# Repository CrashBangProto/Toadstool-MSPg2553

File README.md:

#Toadstool-MSPg2553

**Toadstool Development Board - MSP430G2553**

The Toadstool family is made up of breadboard-friendly prototyping boards that house a microcontroller, and modules called *Caps* that connect using a standard header.  The prototyping board is analagous to an Arduino/Launchpad and the Cap analagous to a shield/boosterpack.

This repository contains the schematics for the **Toadstool-MSPg2553** prototyping board, a breadboard-friendly PCB that houses the Texas Instruments MSP430G2553 microcontroller.

The boards were layed out using [KiCad](http://www.kicad-pcb.org) - KiCad is open source and awesome.

There are a number of other CrashBangProto respositories containing the schematics for other Toadstool boards and Caps, as well as sample code to get you up and running.

Visit the [Toadstool Webpages](http://www.crash-bang.com/projects/toadstool/) for more information on the project.

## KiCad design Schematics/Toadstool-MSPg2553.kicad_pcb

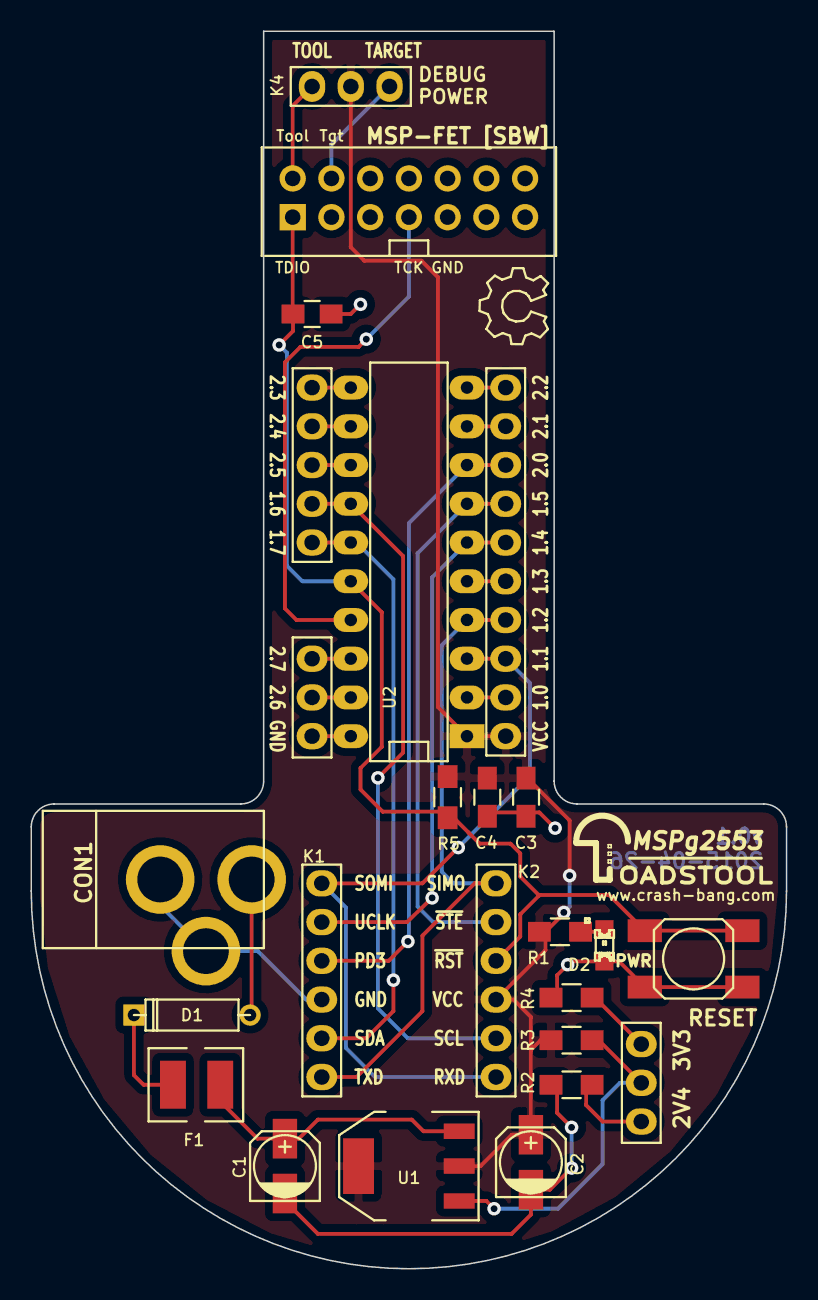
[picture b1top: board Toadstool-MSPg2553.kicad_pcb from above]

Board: 2 copper layers, 49.5 x 81.2 mm, 26 parts (0 on the bottom side), 29 nets.

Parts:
C1, C2: 10uF; c_elec_4x5.3
C3: 10uF; C_0805_HandSoldering
C4: 100nF; C_0805_HandSoldering
C5: 1nF; C_0805_HandSoldering
CON1: BARREL_JACK; BARREL_JACK_No_Slot
D1: DIODE; Diode_D3
D2: PWR; LED-0805
F1: 750mA; MiniSMDPTC-4532
K1: CAP_CONN_LHS; Socket_Strip_Straight_1x06
K2: CAP_CONN_RHS; Socket_Strip_Straight_1x06
K3: V-SELECT; Pin_Header_Straight_1x03
K4: DEBUG_PWR; Pin_Header_Straight_1x03
K5: PIN_18-20; Pin_Header_Straight_1x03
K6: MSP-FET; MSP-FET_Header
K7: PIN_1-10; Pin_Header_Straight_1x10
K8: PIN_11-15; Pin_Header_Straight_1x05
R1: R330; R_0805_HandSoldering
R2: 120R; R_0805_HandSoldering
R3: 110R; R_0805_HandSoldering
R4: 200R; R_0805_HandSoldering
R5: 47k; R_0805_HandSoldering
SW1: RESET; Switch_SMT_Alps_SKQGAxE010
Toadstool_Logo: LOGO**; Toadstool_Logo
U1: LD1117; SOT-223
U2: MSP430G2553; DIP-20_IC

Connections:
/2.4V: K3.1, R3.2
/3.3V: K3.3, R4.2
/P1.0: K7.2, U2.2
/P1.1: K1.1, K2.6, K7.3, U2.3
/P1.2: K1.6, K2.1, K7.4, U2.4
/P1.3: K7.5, U2.5
/P1.4: K1.2, K7.6, U2.6
/P1.5: K2.2, K7.7, U2.7
/P1.6: K2.5, K8.2, U2.14
/P1.7: K1.5, K8.1, U2.15
/P2.0: K1.3, K7.8, U2.8
/P2.1: K7.9, U2.9
/P2.2: K7.10, U2.10
/P2.3: K8.5, U2.11
/P2.4: K8.4, U2.12
/P2.5: K8.3, U2.13
/P2.6: K5.2, U2.19
/P2.7: K5.3, U2.18
/RST: C5.1, K2.3, K6.1, R5.1, SW1.2, U2.16
GND: C1.2, C2.2, C3.1, C4.1, C5.2, CON1.2, CON1.3, D2.2, K1.4, K5.1, K6.9, R3.1, R4.1, SW1.1, U2.20
unnamed: C1.1, F1.1, U1.3
unnamed: CON1.1, D1.1
unnamed: D1.2, F1.2
unnamed: D2.1, R1.1
unnamed: K3.2, R2.1, U1.1
unnamed: K4.1, K6.2
unnamed: K4.3, K6.4
unnamed: K6.7, U2.17
VCC: C2.1, C3.2, C4.2, K2.4, K4.2, K7.1, R1.2, R2.2, R5.2, U1.2, U2.1

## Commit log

2015-05-15 :tada: Added .gitattributes
